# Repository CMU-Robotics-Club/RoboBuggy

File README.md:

RoboBuggy
==============

A project of the [Robotics Club at Carnegie Mellon University](https://roboticsclub.org/).

Buggy (also called Sweepstakes) is a race held annually since 1920 at Carnegie Mellon. Teams of 5 athletes (the pushers) push an un-motorized vehicle (a buggy) containing a driver around a 0.84 mile course in a relay format where the vehicle serves as the baton. Roughly half of the course is uphill, during which the pushers run and shove the buggy uphill. During the other - downhill - half, drivers are on their own to navigate tight turns at speeds of up to 35mph.

Borrowed from the [CMU Buggy Alumni Association](http://cmubuggy.org/reference/What_is_buggy%3F). Visit them to find out more.

In the robotics club we seek to ~~help out robot overlords~~ automate everyone and everything, so we're trying hard to replace a traditional buggy driver with our AI. Alice (the AI) successfully rolled on Raceday for the first time during Carnival 2017!

_Team picture from Raceday 2015._

_Trevor pushing Singularity on Hill 4 during early morning rolls._

## The Buggies 

<table>
<thead>
<tr>
<th align="center" width="50%">Singularity</th>
<th align="center" width="50%"><del>Toothless</del> Transistor</th>
</tr>
</thead>
<tbody>
<tr>
<td align="center"></td>
<td align="center"></td>
</tr>
<tr>
<td align="center">Inherited from a past incarnation of this project, Singularity has been rolling since 1999. She features a bolted aluminum frame that was originally built around a desktop computer. These days, she features a stylish mount for a Surface on top with the control electronics inside.</td>
<td align="center">Transistor was built for the 2015 season using modern carbon fiber shell technology. She was built to be accessible and maintainable as a platform for the future of Robobuggy. Debate within the team on what style she would wear was so fierce we chose to paint her chalkboard black, complete with a new chalking each race.</td>
</tr>
</tbody>
</table>

Looking for more technical docs? [Check out the wiki!](https://github.com/CMU-Robotics-Club/RoboBuggy/wiki)

## System Overview

```
+-----------------+
|   Follow Car    |
|        +        |
|  Safety Driver  |
+-----------------+
         ||
         ||
         \/
+------------------+   +-------------------------+
|  Radio Receiver  |   |       Alice (AI)        |
+------------------+   +-------------------------+
         ||                        /\
         ||                        ||
         \/                        \/
+------------------------------------------------+
|           IO and Safety Controller             |
|                  (Arduino++)                   |
+------------------------------------------------+
                        /\
                        ||
                        \/
+------------------------------------------------+
|               Electromechanical                |
|       (Servo, Solenoids, Pots, Encoders)       |
+------------------------------------------------+
                        /\
                        ||
                        ||
         ____           ||
           \            \/
            \   _____________________
            _\./    \______/      \__\
           < ___o_________________o___\ 
--------------------------------------------------

```
_System block diagram._

Our system architecture keeps a human in the loop all the time, even just to hit the emergency stop button. The human driver can either be sending drive commands (for AI training) or monitoring the AI. The command signals from the AI and human are mixed together (depending on operating mode) in the IO controller. Here we also do last level safety checks like stop on disconnection. The IO controller interfaces directly with the electromechanical systems to make braking, steering, and sensing happen. Find more information in the source directories below.

## File Structure 

The software system is separated into two main directories (sections):
* Software -> code executed in real-time on the buggy at a high level, as well as offline and other tools
* Electrical -> code executing on the low-level systems of the buggy, as well as electrical specifications and eCAD

This folder also contains: 
* Pictures for this readme file
* configuration files

## Contributing

We have a [contributions guide](CONTRIBUTING.md) to get you started.

## Sponsors

Special thanks to NVidia for providing Jetsons for us to host Alice on!

Think this project is cool? Please support the [Robotics Club at CMU](https://roboticsclub.org/sponsors/)!

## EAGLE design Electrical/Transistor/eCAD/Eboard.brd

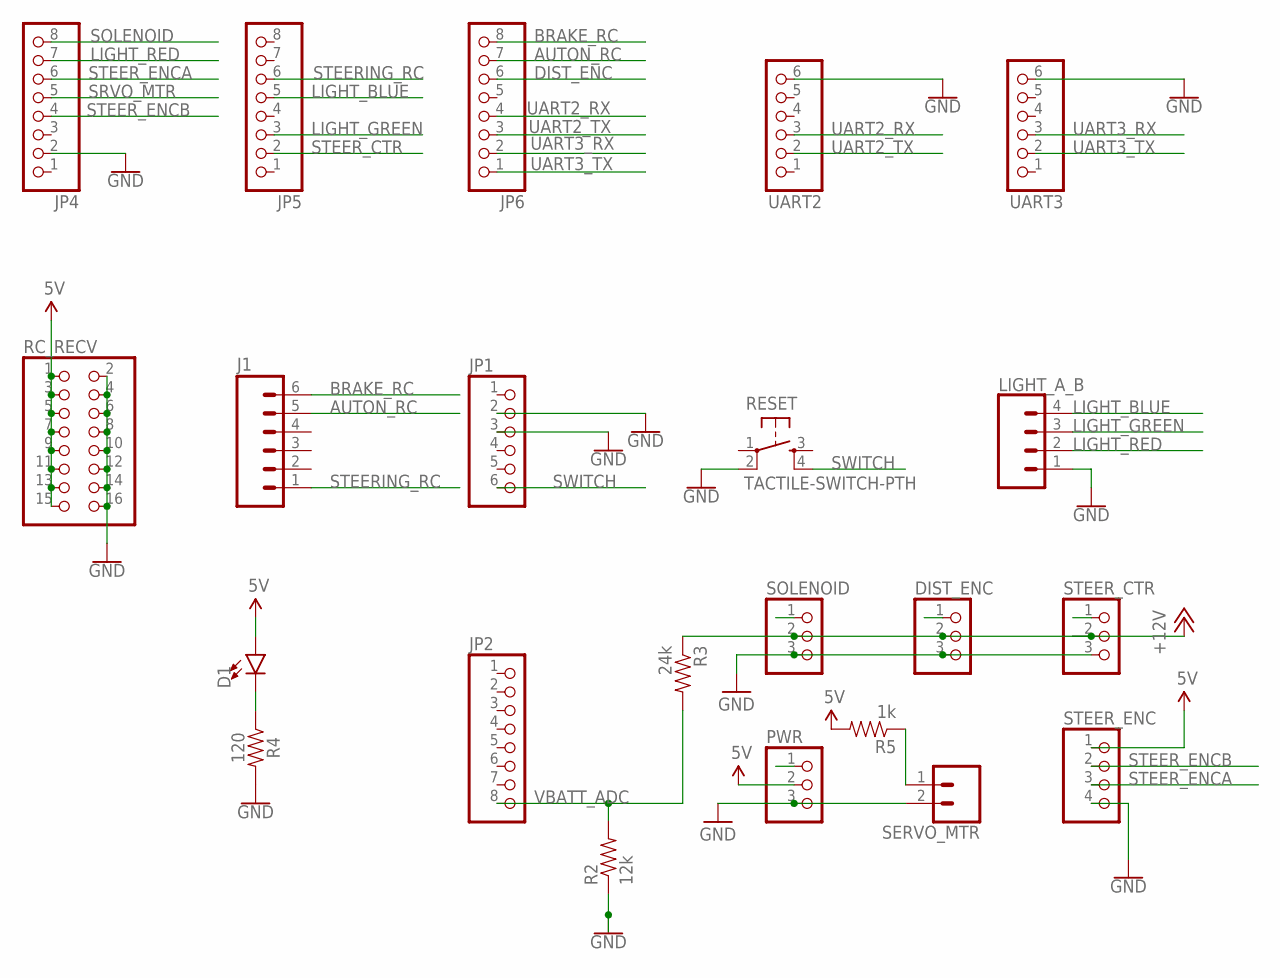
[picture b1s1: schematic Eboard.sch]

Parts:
D1: LED1206; LED-1206
DIST_ENC: PINHD-1X3; 1X03
J1: M06SILK_FEMALE_PTH; 1X06
JP1: PINHD-1X6; 1X06
JP2, JP4, JP5, JP6: PINHD-1X8; 1X08
LIGHT_A_B: CONN_04; 1X04
PWR: PINHD-1X3; 1X03
R2: 12k; AXIAL-0.3
R3: 24k; AXIAL-0.3
R4: 120; AXIAL-0.3
R5: 1k; AXIAL-0.3
RC_RECV: PINHD-2X8; 2X08
RESET: TACTILE-SWITCH-PTH; TAC-SWITCH-PTH
SERVO_MTR: CONN_02; 1X02
SOLENOID: PINHD-1X3; 1X03
STEER_CTR: PINHD-1X3; 1X03
STEER_ENC: PINHD-1X4; 1X04
UART2, UART3: PINHD-1X6; 1X06

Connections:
5V: D1.A, PWR.2, R5.P$2 (2), RC_RECV.1, RC_RECV.3, RC_RECV.5, RC_RECV.7, RC_RECV.9, RC_RECV.11, RC_RECV.13, RC_RECV.15, STEER_ENC.1
12V: DIST_ENC.2, PWR.1, R3.P$1 (1), SOLENOID.2, STEER_CTR.2
AUTON_RC: J1.5, JP6.7
BRAKE_RC: J1.6, JP6.8
DIST_ENC: DIST_ENC.1, JP6.6
GND: DIST_ENC.3, JP1.2, JP1.3, JP4.2, LIGHT_A_B.1, PWR.3, R2.P$1 (1), R4.P$2 (2), RC_RECV.2, RC_RECV.4, RC_RECV.6, RC_RECV.8, RC_RECV.10, RC_RECV.12, RC_RECV.14, RC_RECV.16, RESET.2, SERVO_MTR.2, SOLENOID.3, STEER_CTR.3, STEER_ENC.4, UART2.6, UART3.6
LIGHT_BLUE: JP5.5, LIGHT_A_B.4
LIGHT_GREEN: JP5.3, LIGHT_A_B.3
LIGHT_RED: JP4.7, LIGHT_A_B.2
unnamed: D1.C, R4.P$1 (1)
SOLENOID: JP4.8, SOLENOID.1
SRVO_MTR: JP4.5, R5.P$1 (1), SERVO_MTR.1
STEERING_RC: J1.1, JP5.6
STEER_CTR: JP5.2, STEER_CTR.1
STEER_ENCA: JP4.6, STEER_ENC.3
STEER_ENCB: JP4.4, STEER_ENC.2
SWITCH: JP1.6, RESET.4
UART2_RX: JP6.4, UART2.3
UART2_TX: JP6.3, UART2.2
UART3_RX: JP6.2, UART3.3
UART3_TX: JP6.1, UART3.2
VBATT_ADC: JP2.8, R2.P$2 (2), R3.P$2 (2)

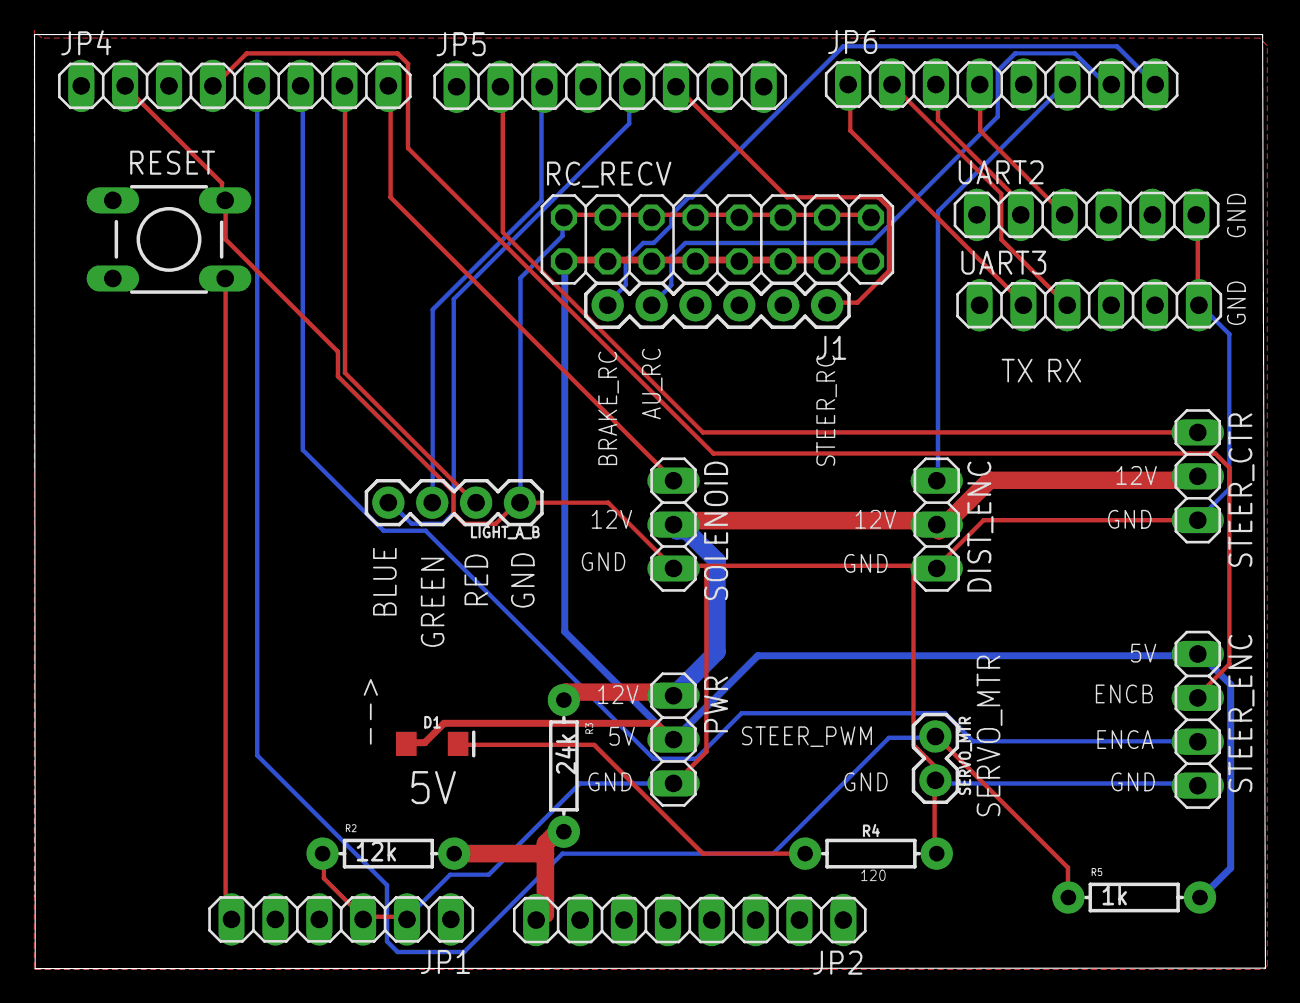
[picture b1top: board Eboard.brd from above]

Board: 2 copper layers, 71.3 x 54.1 mm, 22 parts (0 on the bottom side), 22 nets.

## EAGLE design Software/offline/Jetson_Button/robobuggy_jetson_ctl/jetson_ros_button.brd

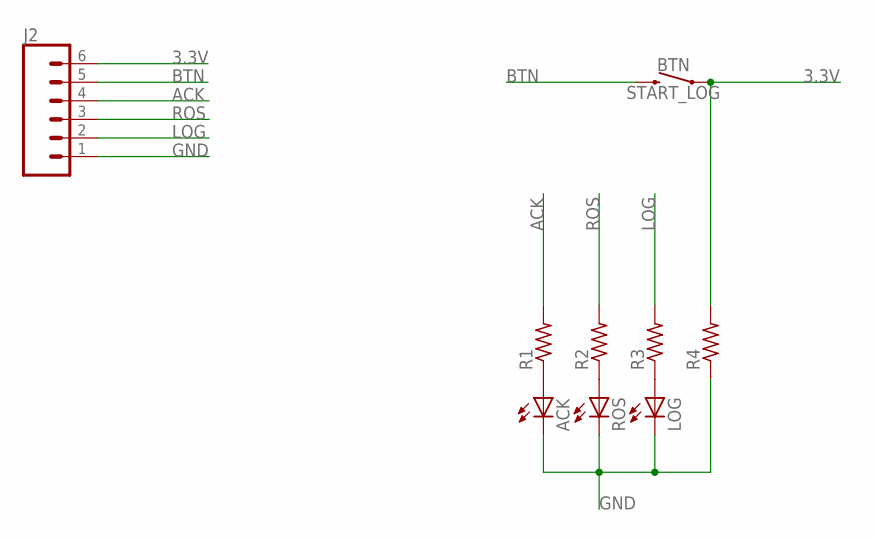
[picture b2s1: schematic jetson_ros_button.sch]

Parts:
ACK: LED_E; LED_1206
BTN: START_LOG; TACTILE_SWITCH_PTH_6.0MM
J2: CONN_06SILK_FEMALE_PTH; 1X06
LOG: LED_E; LED_1206
R1, R2, R3, R4: R-US_0204/7; 0204/7
ROS: LED_E; LED_1206

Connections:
3.3V: BTN.1, J2.6, R4.2
ACK: J2.4, R1.2
BTN: BTN.3 (2), J2.5
GND: ACK.C, J2.1, LOG.C, R4.1, ROS.C
LOG: J2.2, R3.2
unnamed: ACK.A, R1.1
unnamed: R2.1, ROS.A
unnamed: LOG.A, R3.1
ROS: J2.3, R2.2

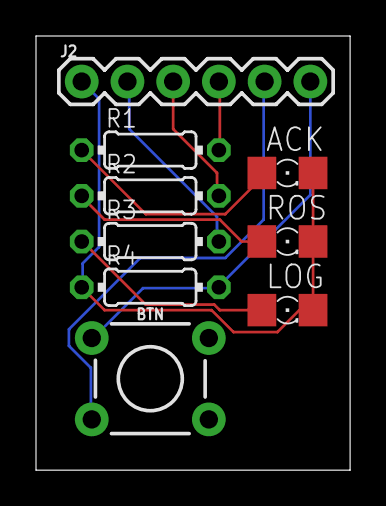
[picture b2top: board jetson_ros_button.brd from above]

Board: 2 copper layers, 17.4 x 24.1 mm, 9 parts (0 on the bottom side), 9 nets.

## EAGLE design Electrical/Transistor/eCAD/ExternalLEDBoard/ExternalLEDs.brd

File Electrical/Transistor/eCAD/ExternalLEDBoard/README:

This folder has the files for the external indicator light board.

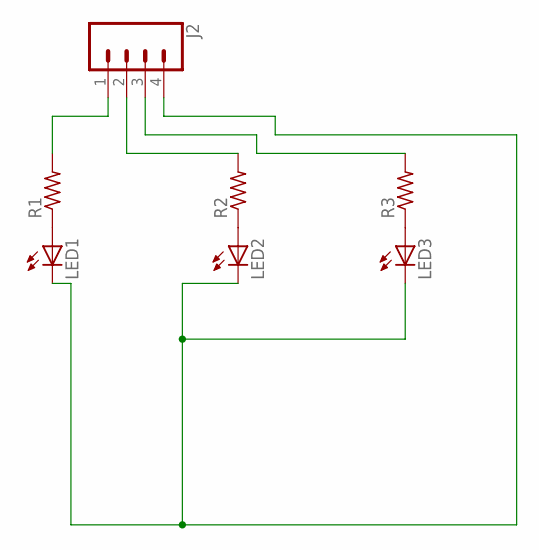
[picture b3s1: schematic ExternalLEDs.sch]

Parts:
J2: CONN_04POLAR; MOLEX-1X4
LED1, LED2, LED3: LED_E; LED_1206
R1, R2, R3: R-US_0204/7; 0204/7

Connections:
unnamed: J2.1, R1.2
unnamed: J2.2, R2.2
unnamed: J2.3, R3.2
unnamed: LED1.A, R1.1
unnamed: LED2.A, R2.1
unnamed: LED3.A, R3.1
unnamed: J2.4, LED1.C, LED2.C, LED3.C

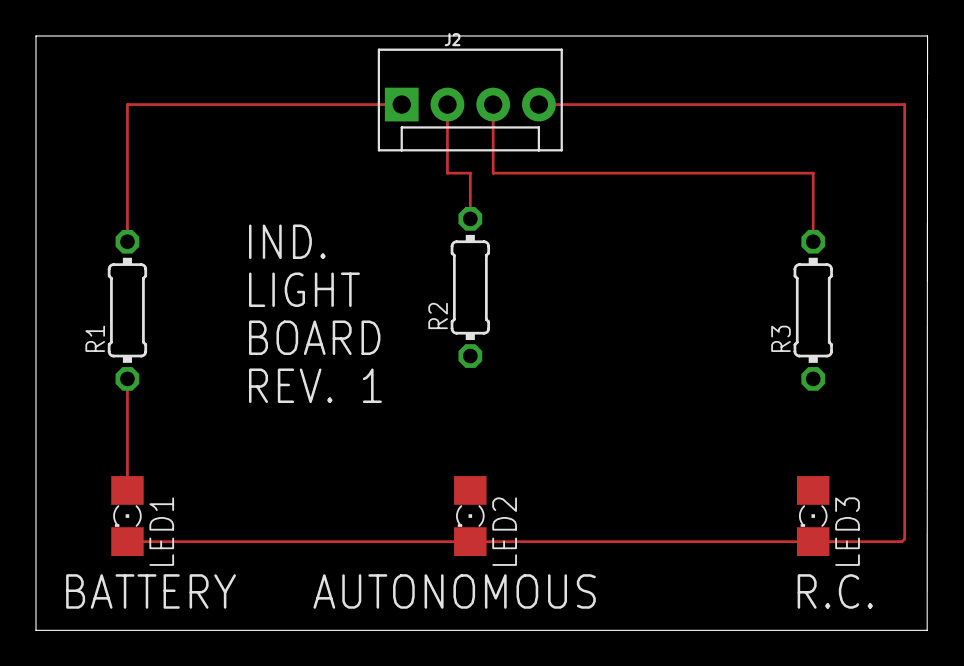
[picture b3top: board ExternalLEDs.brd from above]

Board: 2 copper layers, 49.5 x 33.0 mm, 7 parts (0 on the bottom side), 7 nets.

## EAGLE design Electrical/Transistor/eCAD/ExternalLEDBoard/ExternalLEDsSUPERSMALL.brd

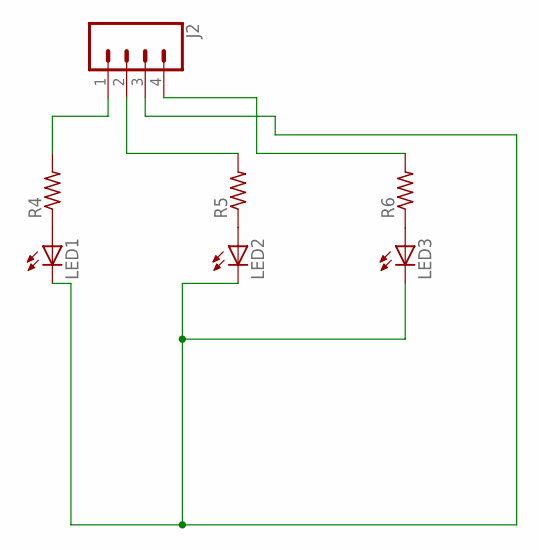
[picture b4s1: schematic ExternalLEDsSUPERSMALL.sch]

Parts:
J2: CONN_04POLAR; MOLEX-1X4
LED1, LED2, LED3: LED_E; LED_1206
R4, R5, R6: R-US_M1206; M1206

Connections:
unnamed: J2.1, R4.2
unnamed: J2.2, R5.2
unnamed: J2.4, R6.2
unnamed: LED1.A, R4.1
unnamed: LED2.A, R5.1
unnamed: LED3.A, R6.1
unnamed: J2.3, LED1.C, LED2.C, LED3.C

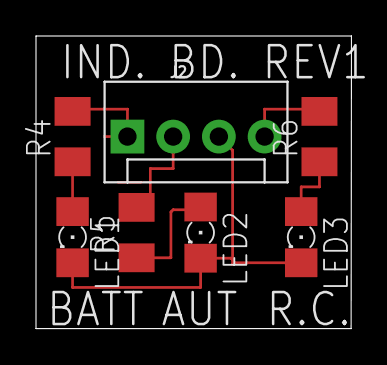
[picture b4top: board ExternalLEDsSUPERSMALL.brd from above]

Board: 2 copper layers, 17.5 x 16.3 mm, 7 parts (0 on the bottom side), 7 nets.

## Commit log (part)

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2017-04-17 Bypass the centering function at boot
2017-04-18 added untested course correction code
2017-04-19 this will go down as one of the ballsiest moves in the history of the project added untested better path tracker
2017-04-26 raceday commit
2017-04-30 moved all the data from the current state matrix into the rest of the fields of the GPSPoseMessage
2017-05-05 removed cancerous commented code
2017-05-05 fixed sim tools
2017-05-05 fixed static analysis inconsistencies we may want to consider disabling those checks
2017-05-05 Cleaned up RobobuggyMainFile
2017-05-05 Removed unused controller code from WayPointFollowerPlanner
2017-05-20 removing duplicate method
2017-05-20 removed localizer.java
2017-05-21 renaming constants
2017-05-21 deleted unnecessary folder
2017-05-23 fixing style on most things
2017-05-25 Removed file notes.txt in offline/localizer per Vivaan's comments
2017-05-25 Cleaning up code
2017-05-26 fixed findbugs issues
2017-05-29 Hopefully did it correctly this time - without getting any config files into the repo
2017-07-22 Initial ROS workspace with IMU/GPS messages and dummy nodes
2017-07-26 Clean up new Quadrature and Rotary class
    Mostly changes that would permit compilation
    Also changed that main actually uses the new Rotary class and not the
    Encoder one.
2017-07-27 Makefile with specific flag for C++
    Thus remove the warning due to the use of non-sensical flags for C++
    compared to the one used for C
2017-07-28 Cleaning up encoder classes
2017-07-30 Resolved compilation issues
2017-08-18 Added in a dummy encoder node
2017-08-23 added launch file with some sample parameters
2017-09-15 Converted IMU broadcaster into a class so that we can test it with gtest Other nodes will be converted soon
2017-09-15 moved everything into node-specific folders and added controller runner
2017-09-15 Added encoder runner (And made some stuff private in the imu broadcaster)
2017-09-16 Fixed runner for GPS Broadcaster Fixed other build issues Will try on Jetson soon
2017-09-17 Implemented low-level communication node
2017-09-17 Converted low-level broadcaster to class
2017-09-18 Confirmed working on VM to buggy
2017-09-18 changed one of the comments that should reference previous commit changes
2017-09-24 File restructure
2017-09-25 Added in skeleton files of localizer
2017-09-25 Moved rbsm_config.txt
2017-09-25 Updated scripts and Makefile to reflect directory reorganization. Updated .gitignore for same reason
2017-09-25 removed old localizer files
2017-09-27 Added in matrix initialization routine
2017-09-29 FINISHED LOCALIZER
2017-09-29 added in GPS broadcaster
2017-09-29 Fixed parameter fetching
2017-09-30 Started writing IMU node
2017-09-30 Updated IMU message and added skeleton of broadcaster/parser
2017-09-30 Working on making IMU broadcaster build
2017-10-01 updated dev nodes to new udev rules
2017-10-01 Adding CAD files for arduino shield
2017-10-02 Updated readme with instructions for libfreespace
2017-10-02 Deleted spoof nodes
2017-10-03 Updated gitignore to discard vim swap files
2017-10-05 Initial implementation of serial message parsing
2017-10-06 Fixed baud rate issue, added logs/ to .gitignore
2017-10-06 fixed indentation
2017-10-06 Very simple hellonode server
2017-10-06 Initial Server setup
2017-10-06 Added new folder for the external LED board cad files
2017-10-06 Updated Indicator LEDs Board
    Added text labels to the surface mount LEDs
    Added a title to the overall board
    Removed extraneous text
2017-10-06 This is a new folder for the indicator light board files.
2017-10-06 Updated the EAGLE Schematic/Board
    -Changed connection type to 4-pin plug-in.
    -Changed text to the correct layer.
    -Redid on-board routing.
2017-10-06 Deleting useless files #2
2017-10-06 Added in preliminary flowcharts for GPS Node
2017-10-07 Updating rbsm_console to reflect changes in system baud rate and folder reorganization
2017-10-07 Cleaned up Rotary class to resolve encoder tick not properly incrementing
2017-10-08 Increased margins/tolerances on XSMALL version.
    Now the LED labels are a little further from the actual LEDs, and there is some margin on each side of the Revision Label.
    Revision Label is also on the back now, allowing us to reduce cost by 7.5 cents.
2017-10-08 Fixed DRC errors and added a copper GND plane.
2017-10-08 Increased isolation value on GND pours to 12 mils to improve manufacturing error tolerances
2017-10-09 Renamed files and moved them around
2017-10-09 Removed old code
2017-10-09 General cleanup of nodes
2017-10-11 Modified controller to have skeleton of implementation
2017-10-12 Ported returnBrakeValue
2017-10-13 added in rest of the ported controller
2017-10-30 initial implementation of serial node controller
2017-10-30 Removed unnecessary message files
2017-11-01 Working serial command node
2017-11-03 Because messages were getting backed up, we decided to publish at a fixed rate of 0.5Hz
2017-11-04 Committing to work on quickfixes for serial
2017-11-05 Fixed a few small things with the localizer
2017-11-05 Slight modifications and touch-ups
2017-11-05 Fixed issues with the localizer
    - northing and easting were switched accidentally
    - previous encoder ticks was uninitialized which caused weird issues
    when trying to run the filter
2017-11-09 Restored launch file
2017-11-11 removed accidental inclusion of characters
2017-11-11 switched mapping for red and blue LEDS
2017-11-13 Forgot to commit file from master merge
2017-11-17 Added all Brake messages and two Diagnostics messages (auton state and error) to web server JSON publisher
2017-11-27 Added Brake to imports
2017-11-30 (vivaan) Made sure to fully zero out the IMU config message, added in more feedback and added in the IMU node to the launch file
2017-12-01 Web server v1.0 tested and deployed
2017-12-16 Updated controller simulation files
2018-01-01 Add the push button to the PCB
2018-01-23 removed bad import
2018-01-26 performed autorouter and drc, about to change 5v to 16mils and 12v to 40mils.
2018-01-26 finished minor overlap errors on board and did ground fill
2018-01-26 Modify JSON for new message structure
2018-01-30 data_map_plot.py is updated Now subscribes to Pose instead of GPS Now should correctly display orientation data from heading_rad Still no feature for steering data Will add
2018-02-01 made all the lines on schematic uniform, added ground and 5V symbols, rearranged groupings for ease of understanding, rerouted board so that wires were less messy, added 5V diode silkscreen
2018-02-01 put resistor in series and resolved trace issues on board
2018-02-01 verified edge dimensions on the board and that the board followed oshpark drc rules before doing top and bottom ground fills for board
2018-02-02 Fixed issue where localizer would output NaN as estimate
    Was because the time conversion was done on two ints and expected a number less than 1, which led to a divide-by-0
2018-02-07 fixed issues with localizer orientation
2018-02-10 updated dimensions, reversed the JP1 pin set, reversed JP2 so that VBATT would be in pin A0, reversed all thre three-pin connections to match existing pin plug in configuration, updated R4 resistor t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
2018-02-10 reversed steering pins to match configuration of existing connector
2018-02-12 commented arduino pins for shield
2018-02-12 added 12V silkscreen, changed servo mtr to two-pin connector, rerouted accordingly
2018-02-12 Framework for controller simulator node
2018-02-16 Remove dead code
2018-02-18 Fixes the translator node as requested by Vivaan
2018-02-20 modified distances between pins so that they will align with the mega, then modified back silkscreen to robobuggy rev 1.8.1
2018-02-25 Almost finished with node Need to work on conversion from UTM to degrees
2018-02-26 Updated launch file to reflect correct names of nodes
2018-02-28 removed gps impact on heading from localizer
2018-03-01 Forgot one
2018-03-02 fixed localizer initialization
    mixed up utm easting and northing again
    hurr durr
2018-03-04 Fixes to launch file for parameters
2018-03-19 made fixes to controller simulator
2018-03-22 added NANDistor folder
2018-03-23 Changed IMU initialization so it's on Full Motion ON mode. Previously it was Full Motion Mode, which would stop outputting IMU sensor readings when the device went to sleep
2018-03-31 Porting dynamixel servo code for NANDsistor
2018-03-31 got the servo messages to work by fprintfing
2018-03-31 Changed the dynamixel servo command method to work with the new UART implementation
2018-04-01 added in honeywell imu orientation
2018-04-04 big set of changes to make sure the whole stack works
2018-04-06 fixed localizer heading
2018-04-12 Working IMU orientation (finally)
2018-04-13 adding skeleton code for GPS broadcaster
2018-04-13 added cpp11 support because of the new jsoncpp library
2018-04-13 removed misplaced skeleton
2018-04-16 adding flowchart for the controller simulator
2018-04-18 adding more tests for GPS Broadcaster
2018-04-24 general cleanup added comments to tests and moved a comment over from inside to outside a method
2018-04-30 Revert "made requested changes for pull request" reverting to get rid of unnecessary files from java_src This reverts commit 00beed2bb8fbe02844af8c85ee35ac3599fc94f6.
2018-05-05 last fixes before merging
2018-05-19 added first part of full system simulation
2018-06-12 (untested) finished the implementation of the simulator, and added visualization hooks into the data_map_plot
2018-06-19 Modified docs for data map plot node
2018-06-24 Added documentation flowchart and source
2018-06-26 Forgot a couple semicolons
2018-07-13 added blank file for rewrite
2018-08-31 added flowchart source
2018-09-01 updated flowchart to clarify two spots
2018-09-07 added the kalman update code, and reformatted all the arrays to have a single q and c matrix
2018-09-16 When it auton mode and RC timeout made it so that when Radio connection was regained, the RC timeout light turns off
2018-09-18 tweaked matrices
2018-09-18 added in imu support to the full system sim tweaked the matrices some more
2018-09-18 more tweaking
2018-09-20 Added relative pathing to source the waypoint files so that we dont have to keep changing the full filepath
2018-09-23 added test file and doc file
2018-10-05 added cals to localizer
2018-10-05 localizer cals redo
2018-10-05 Revert "added cals to localizer" need to undo this This reverts commit 1108d9ab2ee51098d2a46f77beb40f29921d6e33.
2018-11-02 the node name was invalid, fixed it
2018-11-02 removing unnecessary python file
2018-11-03 minor fixes made
2018-11-07 added true north offset
2018-11-07 fixed reading from flash memory
2018-11-09 fixed line endings
2018-11-09 modified sweep test
2018-11-10 added controller back into launch file
2018-11-12 added the functions for onboard buggy and for radio controller
2018-11-13 added sensor periods
2018-11-16 minor fixes
2018-12-01 Add cv_poc folder and readme
2019-01-19 fix video and coordinates
2019-01-25 increased gain and removed "lowpass filter" from IMU
2019-01-25 added documentation file
2019-01-26 updated docs
2019-01-28 added skeleton for collison algo fixed relative loc formula so we take buggy frame into account
2019-01-29 filled out basic untested collision avoidance
2019-02-15 working mobilenet classifier
2019-02-25 controller tuning
2019-03-01 bug fixes
2019-03-02 changed radians to degrees; GUI modifications
2019-03-29 minor changes
2019-04-08 added dynamixel support, removed low level entirely
2019-11-01 updating to current state
2020-01-24 added the code for servo board
2020-01-25 adding factory reset code
2020-01-31 edited the servo board to work with i2c

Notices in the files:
parts and their libraries:
SparkFun-LED: Licensing: Creative Commons ShareAlike 4.0 International - https://creativecommons.org/licenses/by-sa/4.0
